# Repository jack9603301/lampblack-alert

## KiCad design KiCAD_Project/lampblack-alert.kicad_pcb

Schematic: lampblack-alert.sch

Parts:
J1: 0-5VADC; PinHeader_1x01_P2.54mm_Vertical
J2, J4: GND; PinHeader_1x01_P2.54mm_Vertical
J3: 0-3VADC; PinHeader_1x01_P2.54mm_Vertical
R1: 10k; R_Axial_DIN0204_L3.6mm_D1.6mm_P1.90mm_Vertical
R2: 20k; R_Axial_DIN0204_L3.6mm_D1.6mm_P1.90mm_Vertical

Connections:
unnamed: J1.1, R1.1
unnamed: J2.1, J4.1, R2.2
unnamed: J3.1, R1.2, R2.1

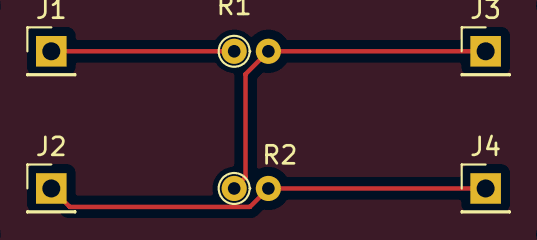
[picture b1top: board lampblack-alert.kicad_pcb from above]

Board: 2 copper layers, 6 parts (0 on the bottom side), 3 nets.

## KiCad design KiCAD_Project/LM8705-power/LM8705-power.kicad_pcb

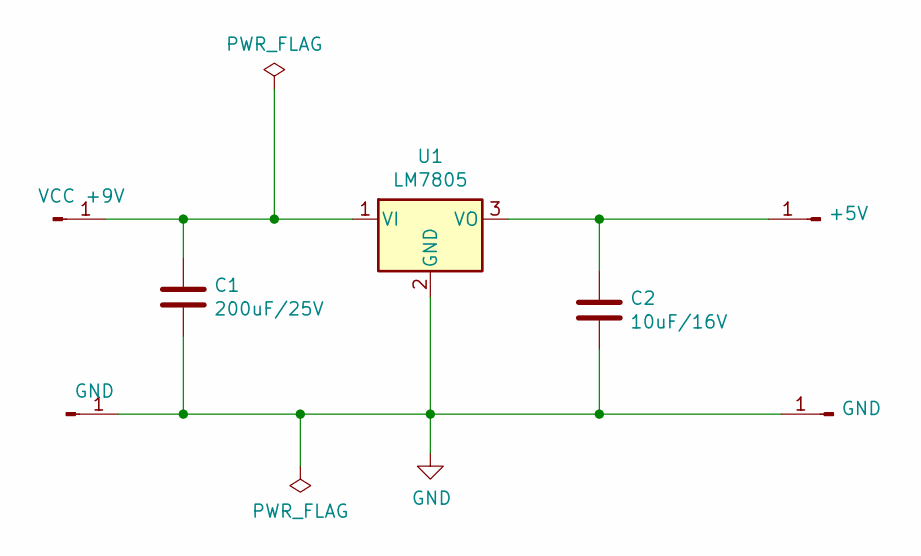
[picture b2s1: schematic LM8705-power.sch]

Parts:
C1: 200uF/25V; CP_Radial_D4.0mm_P2.00mm
C2: 10uF/16V; CP_Radial_D4.0mm_P2.00mm
J1: VCC +9V; PinHeader_1x01_P2.54mm_Vertical
J2, J3: GND; PinHeader_1x01_P2.54mm_Vertical
J4: +5V; PinHeader_1x01_P2.54mm_Vertical
U1: LM7805; TO-220-3_Vertical

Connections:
GND: C1.2, C2.2, J2.1, J3.1, U1.2 (GND)
unnamed: C1.1, J1.1, U1.1 (VI)
unnamed: C2.1, J4.1, U1.3 (VO)

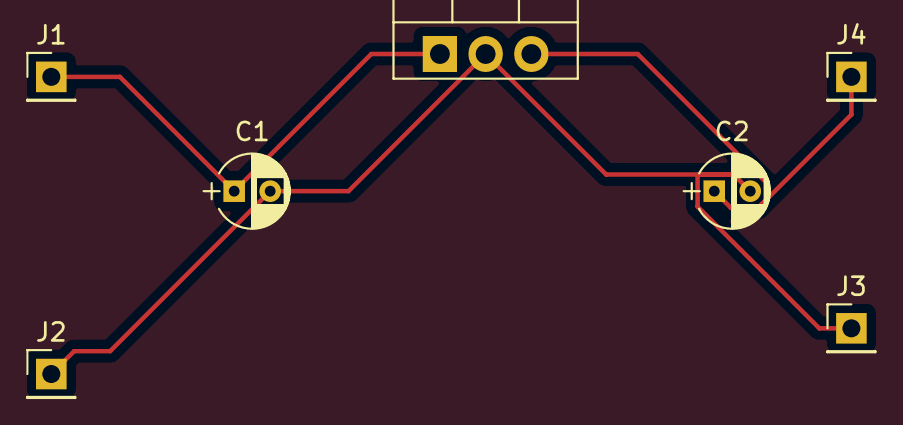
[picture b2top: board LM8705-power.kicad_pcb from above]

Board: 2 copper layers, 7 parts (0 on the bottom side), 3 nets.

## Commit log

2021-08-08 创建项目,敏感数据脱敏
2021-08-11 支持info
2021-08-13 计算模拟量
2021-08-14 重命名： lamblack-alert.yaml -> lampblack-alert.yaml
2021-08-15 支持状态和调试模式
2021-08-17 校准公式
2021-08-19 背光板控制
2021-08-19 硬件设计和PCB
